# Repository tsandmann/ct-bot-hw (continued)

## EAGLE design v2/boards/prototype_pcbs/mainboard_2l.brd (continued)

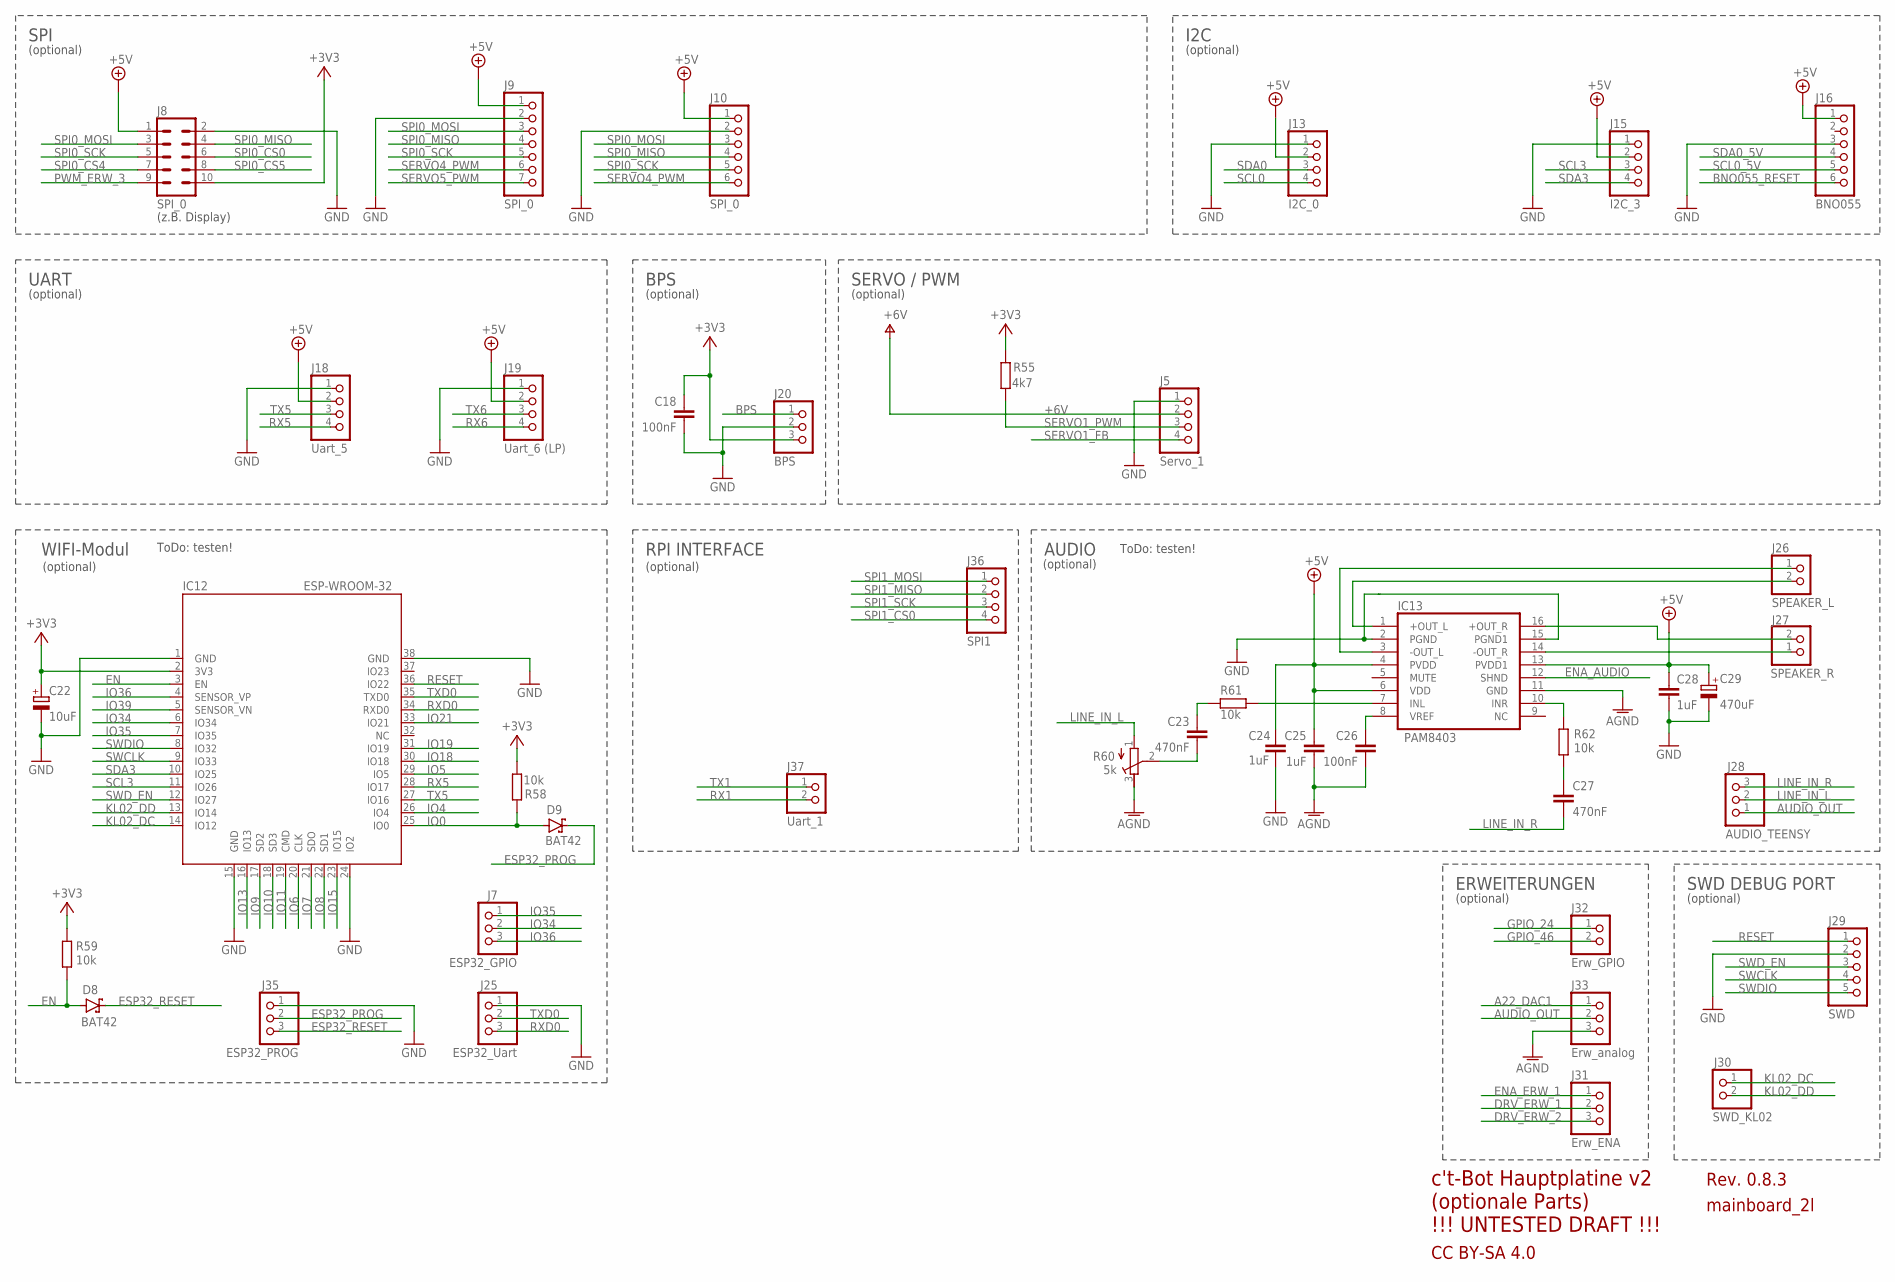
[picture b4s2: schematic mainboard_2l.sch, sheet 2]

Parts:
C18, C26: 100nF; C025-025X050
C22: 10uF; E2,5-5
C23, C27: 470nF; C025-025X050
C24, C25, C28: 1uF; C025-025X050
C29: 470uF; E3,5-8
D8, D9: BAT42; 0207/2V
IC12: ESP-WROOM-32
IC13: PAM8403; SOP-16
J5: Servo_1; 1X04
J7: ESP32_GPIO; 1X03
J8: SPI_0; ML10
J9: SPI_0; 1X07
J10: SPI_0; 1X06
J13: I2C_0; 1X04
J15: I2C_3; 1X04
J16: BNO055; 1X06
J18: Uart_5; 1X04
J19: Uart_6 (LP); 1X04
J20: BPS; 1X03
J25: ESP32_Uart; 1X03
J26: SPEAKER_L; 1X02
J27: SPEAKER_R; 1X02
J28: AUDIO_TEENSY; 1X03
J29: SWD; 1X05
J30: SWD_KL02; 1X02
J31: Erw_ENA; 1X03
J32: Erw_GPIO; 1X02
J33: Erw_analog; 1X03
J35: ESP32_PROG; 1X03
J36: SPI1; 1X04
J37: Uart_1; 1X02
R55: 4k7; 0204/7
R58, R59, R61, R62: 10k; 0204V
R60: 5k; RTRIM64W

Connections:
+3V3: C18.1, C22.+, IC12.2 (3V3), J8.10, J20.3, R55.2, R58.1, R59.2; also elsewhere on the board
+6V: J5.2; also elsewhere on the board
A22_DAC1: J33.1; also elsewhere on the board
AGND: C25.2, C26.2, IC13.11 (GND), J33.3, R60.3 (E); also elsewhere on the board
AUDIO_OUT: J28.1, J33.2; also elsewhere on the board
BNO055_RESET: J16.6; also elsewhere on the board
BPS: J20.1; also elsewhere on the board
DRV_ERW_1: J31.2; also elsewhere on the board
DRV_ERW_2: J31.3; also elsewhere on the board
EN: D8.1 (A), IC12.3 (EN), R59.1
ENA_AUDIO: IC13.12 (SHND); also elsewhere on the board
ENA_ERW_1: J31.1; also elsewhere on the board
ESP32_PROG: D9.2 (C), J35.2; also elsewhere on the board
ESP32_RESET: D8.2 (C), J35.3; also elsewhere on the board
GND: C18.2, C22.-, C24.2, C28.2, C29.-, IC12.1 (GND), IC12.15 (GND), IC12.24 (IO2), IC12.38 (GND), IC13.2 (PGND), IC13.15 (PGND1), J5.1, J8.2, J9.2, J10.2, J13.1, J15.1, J16.3, J18.1, J19.1, J20.2, J25.1, J29.2, J35.1; also elsewhere on the board
GPIO_24: J32.1; also elsewhere on the board
GPIO_46: J32.2; also elsewhere on the board
IO0: D9.1 (A), IC12.25 (IO0), R58.2
IO4: IC12.26 (IO4)
IO5: IC12.29 (IO5)
IO6: IC12.20 (CLK)
IO7: IC12.21 (SDO)
IO8: IC12.22 (SD1)
IO9: IC12.17 (SD2)
IO10: IC12.18 (SD3)
IO11: IC12.19 (CMD)
IO13: IC12.16 (IO13)
IO15: IC12.23 (IO15)
IO18: IC12.30 (IO18)
IO19: IC12.31 (IO19)
IO21: IC12.33 (IO21)
IO34: IC12.6 (IO34), J7.2
IO35: IC12.7 (IO35), J7.1
IO36: IC12.4 (SENSOR_VP), J7.3
IO39: IC12.5 (SENSOR_VN)
KL02_DC: IC12.14 (IO12), J30.1
KL02_DD: IC12.13 (IO14), J30.2
LINE_IN_L: J28.2, R60.1 (A)
LINE_IN_R: C27.2, J28.3
unnamed: IC13.1 (+OUT_L), J26.2
unnamed: IC13.3 (-OUT_L), J26.1
unnamed: C26.1, IC13.8 (VREF)
unnamed: IC13.7 (INL), R61.1
unnamed: C23.1, R61.2
unnamed: C23.2, R60.2 (S)
unnamed: IC13.14 (-OUT_R), J27.1
unnamed: IC13.16 (+OUT_R), J27.2
unnamed: IC13.10 (INR), R62.1
unnamed: C27.1, R62.2
PWM_ERW_3: J8.9; also elsewhere on the board
RESET: IC12.36 (IO22), J29.1; also elsewhere on the board
RX1: J37.2; also elsewhere on the board
RX5: IC12.28 (IO17), J18.4; also elsewhere on the board
RX6: J19.4; also elsewhere on the board
RXD0: IC12.34 (RXD0), J25.3
SCL0: J13.4; also elsewhere on the board
SCL0_5V: J16.5; also elsewhere on the board
SCL3: IC12.11 (IO26), J15.3; also elsewhere on the board
SDA0: J13.3; also elsewhere on the board
SDA0_5V: J16.4; also elsewhere on the board
SDA3: IC12.10 (IO25), J15.4; also elsewhere on the board
SERVO1_FB: J5.4; also elsewhere on the board
SERVO1_PWM: J5.3, R55.1; also elsewhere on the board
SERVO4_PWM: J9.6, J10.6; also elsewhere on the board
SERVO5_PWM: J9.7; also elsewhere on the board
SPI0_CS0: J8.6; also elsewhere on the board
SPI0_CS4: J8.7; also elsewhere on the board
SPI0_CS5: J8.8; also elsewhere on the board
SPI0_MISO: J8.4, J9.4, J10.4; also elsewhere on the board
SPI0_MOSI: J8.3, J9.3, J10.3; also elsewhere on the board
SPI0_SCK: J8.5, J9.5, J10.5; also elsewhere on the board
SPI1_CS0: J36.4; also elsewhere on the board
SPI1_MISO: J36.2; also elsewhere on the board
SPI1_MOSI: J36.1; also elsewhere on the board
SPI1_SCK: J36.3; also elsewhere on the board
SWCLK: IC12.9 (IO33), J29.4
SWDIO: IC12.8 (IO32), J29.5
SWD_EN: IC12.12 (IO27), J29.3
TX1: J37.1; also elsewhere on the board
TX5: IC12.27 (IO16), J18.3; also elsewhere on the board
TX6: J19.3; also elsewhere on the board
TXD0: IC12.35 (TXD0), J25.2
VCC: C24.1, C25.1, C28.1, C29.+, IC13.4 (PVDD), IC13.6 (VDD), IC13.13 (PVDD1), J8.1, J9.1, J10.1, J13.2, J15.2, J16.1, J18.2, J19.2; also elsewhere on the board

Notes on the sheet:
(optional)
(z.B. Display)
c't-Bot Hauptplatine v2 (optionale Parts) !!! UNTESTED DRAFT !!!
Rev. 0.8.3
CC BY-SA 4.0
mainboard_2l
SPI
I2C
UART
BPS
SERVO / PWM
ERWEITERUNGEN
WIFI-Modul
SWD DEBUG PORT
AUDIO
RPI INTERFACE
ToDo: testen!

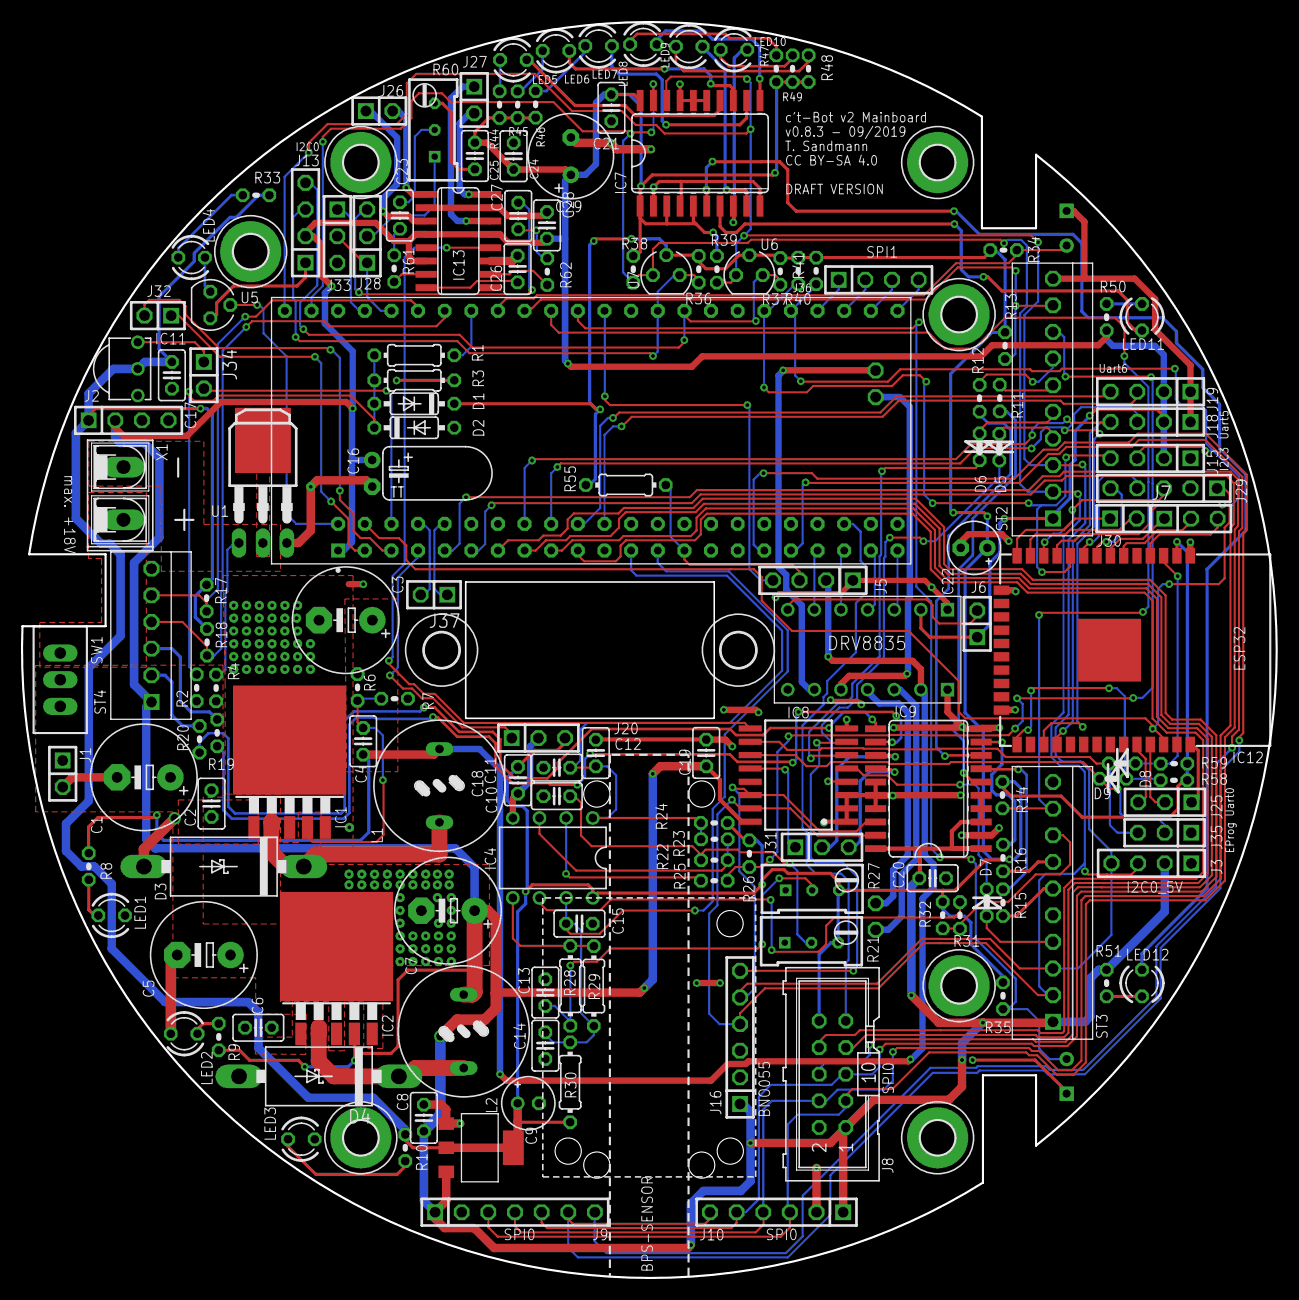
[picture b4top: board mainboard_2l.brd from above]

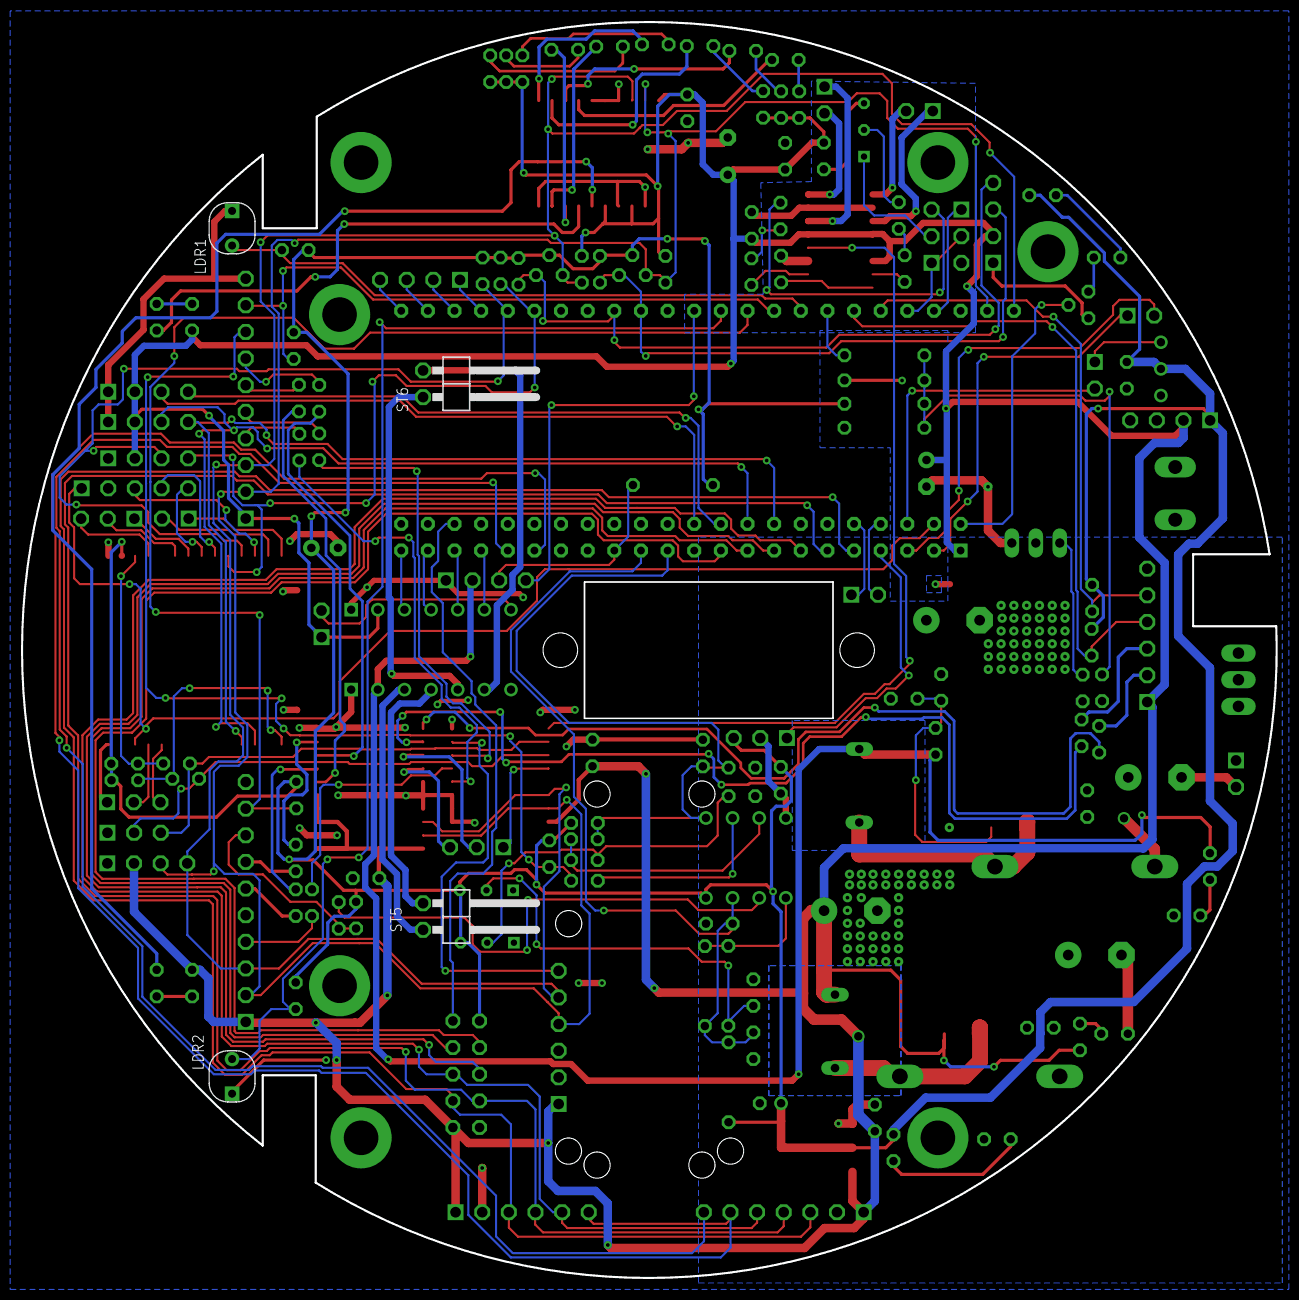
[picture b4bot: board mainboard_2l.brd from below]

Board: 2 copper layers, 119.6 x 119.8 mm, 168 parts (4 on the bottom side), 145 nets.

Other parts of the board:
U$1, U$2, U$3, U$4, U$5, U$6, U$7: 3,3-PAD
U$8, U$9: 3,3

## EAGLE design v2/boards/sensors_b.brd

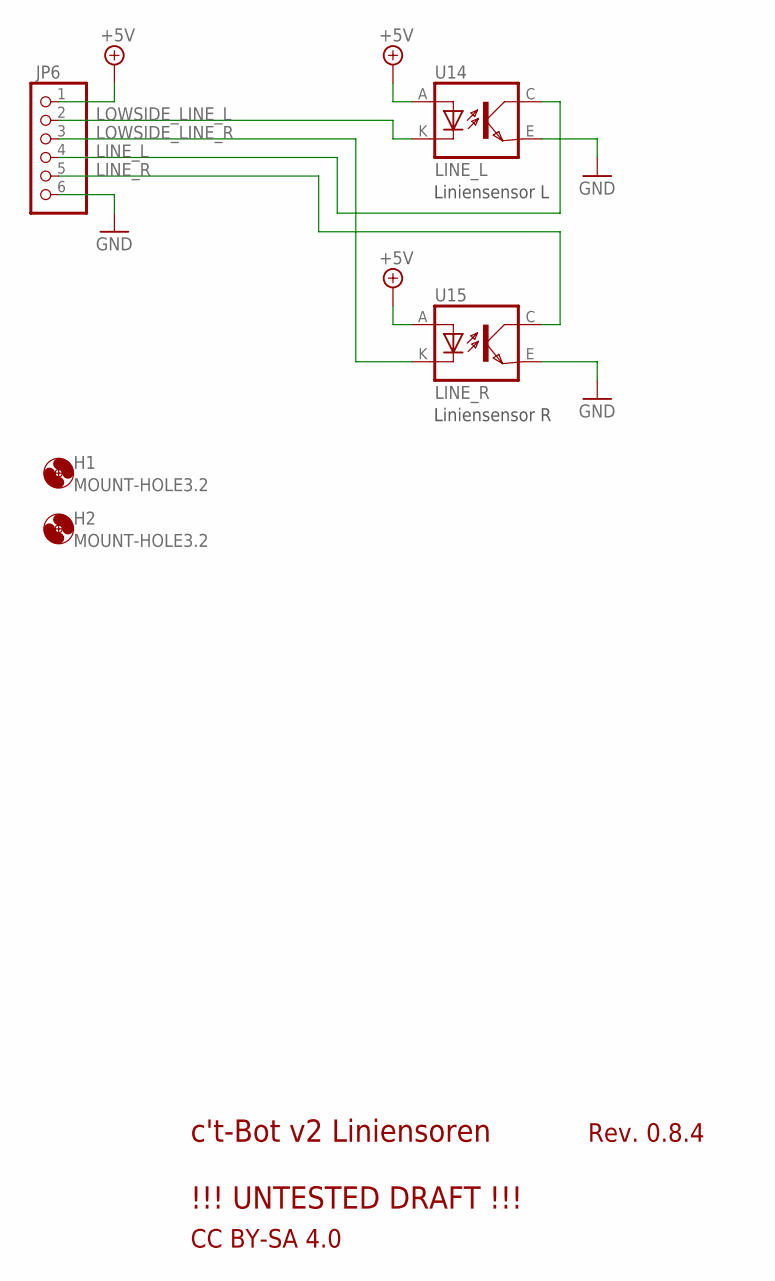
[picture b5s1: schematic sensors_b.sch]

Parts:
H1, H2: MOUNT-HOLE3.2; 3,2
JP6: PINHD-1X6; 1X06
U14: LINE_L; 4
U15: LINE_R; 4

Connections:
+5V: JP6.1, U14.A, U15.A
GND: JP6.6, U14.E (EMI), U15.E (EMI)
LINE_L: JP6.4, U14.C (COL)
LINE_R: JP6.5, U15.C (COL)
LOWSIDE_LINE_L: JP6.2, U14.K (C)
LOWSIDE_LINE_R: JP6.3, U15.K (C)

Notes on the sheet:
c't-Bot v2 Liniensoren !!! UNTESTED DRAFT !!!
Rev. 0.8.4
CC BY-SA 4.0
Liniensensor L
Liniensensor R

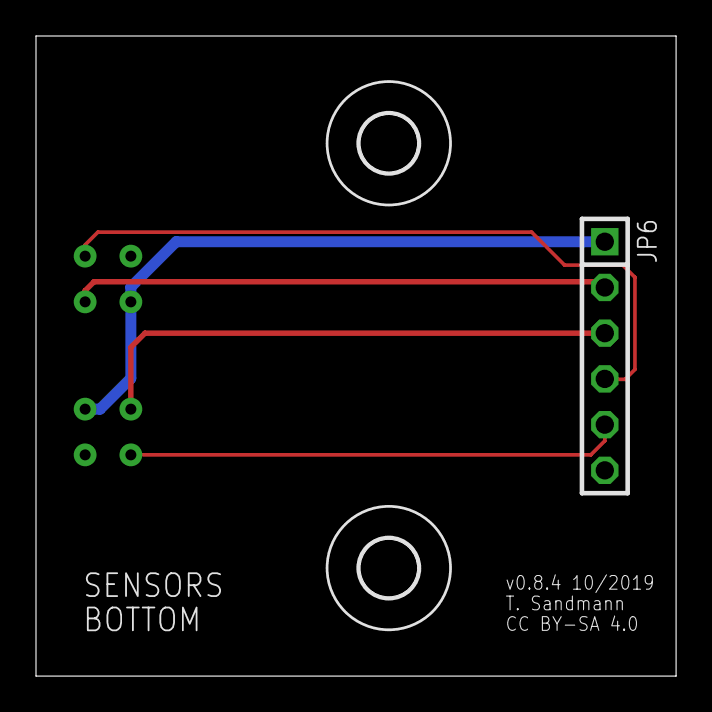
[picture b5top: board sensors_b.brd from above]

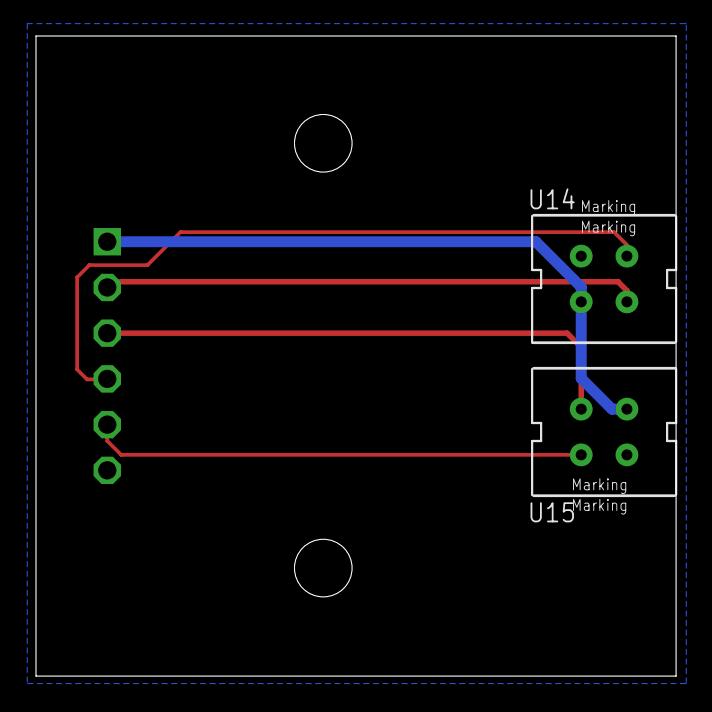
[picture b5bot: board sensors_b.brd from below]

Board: 2 copper layers, 35.6 x 35.6 mm, 5 parts (2 on the bottom side), 6 nets.

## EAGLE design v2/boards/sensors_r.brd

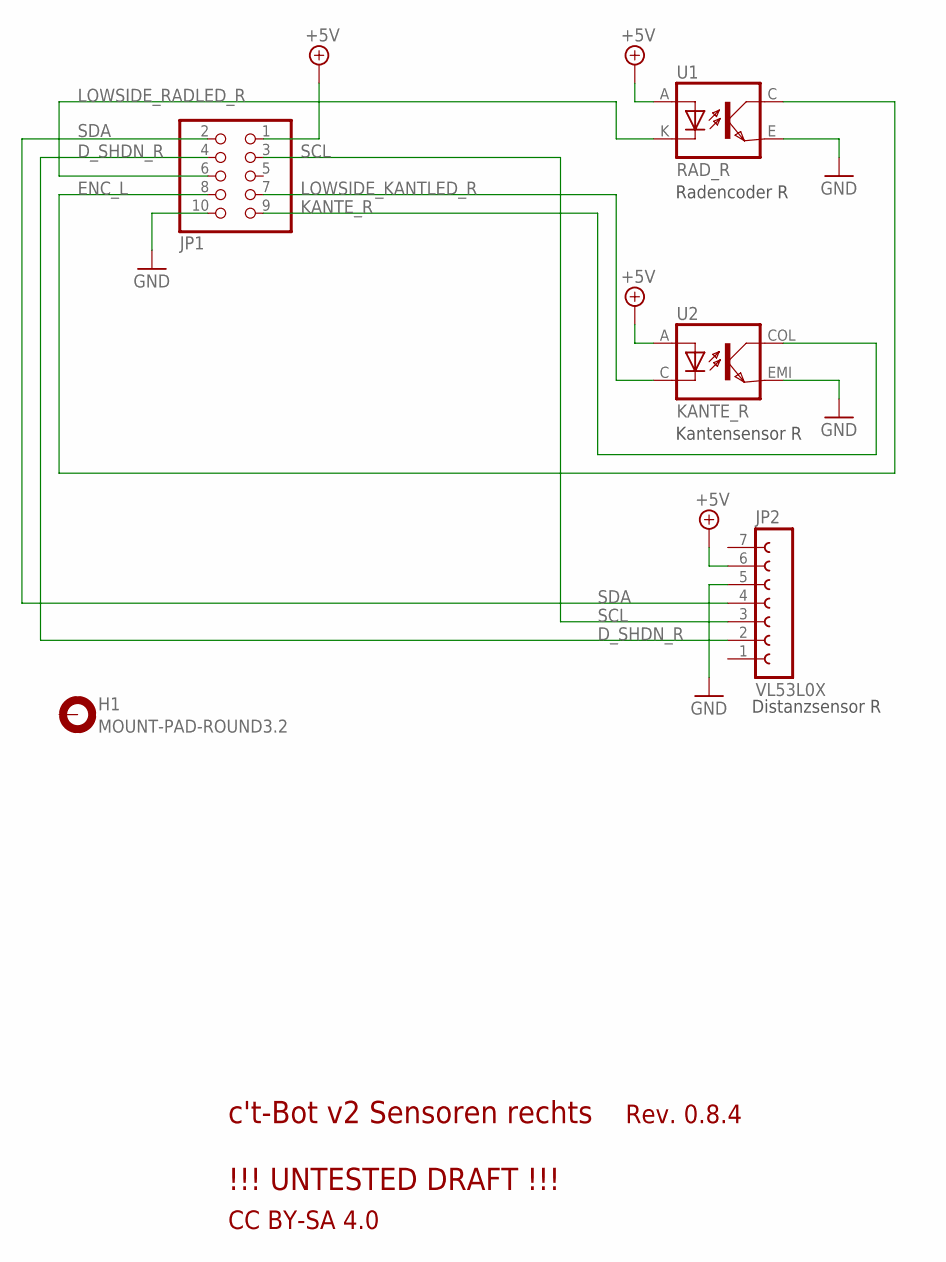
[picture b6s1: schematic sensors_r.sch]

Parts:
H1: MOUNT-PAD-ROUND3.2; 3,2-PAD
JP1: PINHD-2X5; 2X05
JP2: VL53L0X; FE07W
U1: RAD_R; 4
U2: KANTE_R; EDGE

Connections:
+5V: JP1.1, JP2.6, U1.A, U2.A
D_SHDN_R: JP1.4, JP2.2
ENC_L: JP1.8, U1.C (COL)
GND: JP1.10, JP2.5, U1.E (EMI), U2.EMI
KANTE_R: JP1.9, U2.COL
LOWSIDE_KANTLED_R: JP1.7, U2.C
LOWSIDE_RADLED_R: JP1.6, U1.K (C)
SCL: JP1.3, JP2.3
SDA: JP1.2, JP2.4

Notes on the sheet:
c't-Bot v2 Sensoren rechts !!! UNTESTED DRAFT !!!
Rev. 0.8.4
CC BY-SA 4.0
Radencoder R
Kantensensor R
Distanzsensor R

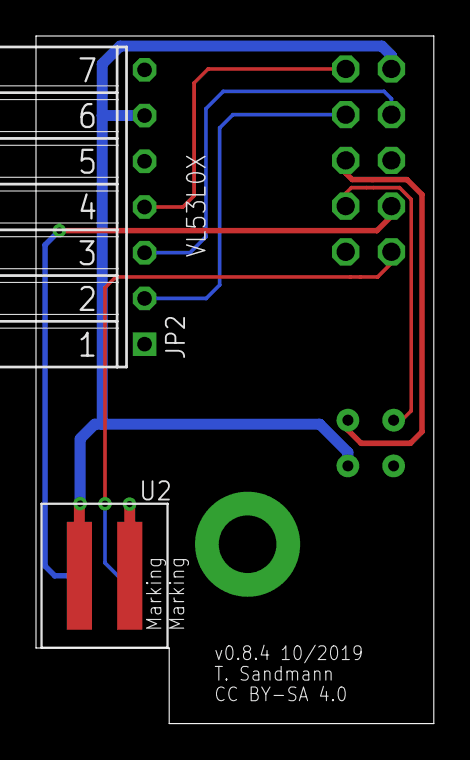
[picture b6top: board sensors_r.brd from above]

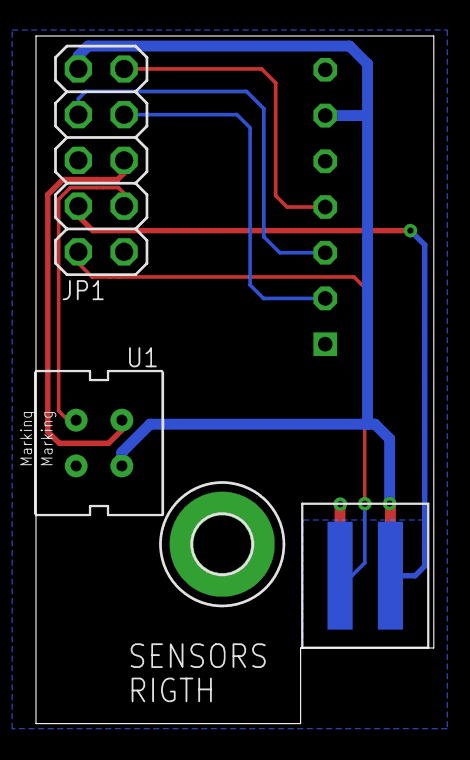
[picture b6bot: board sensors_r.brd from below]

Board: 2 copper layers, 22.1 x 38.2 mm, 5 parts (3 on the bottom side), 9 nets.
